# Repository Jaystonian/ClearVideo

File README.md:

# ClearVideo
Various S-Video devices

2020-10-04 
 * Updated the schematics and pcb to show I am using a 74F04, not a 74F06.. It has always been a '04.
 * Updated CV128 layout slightly.

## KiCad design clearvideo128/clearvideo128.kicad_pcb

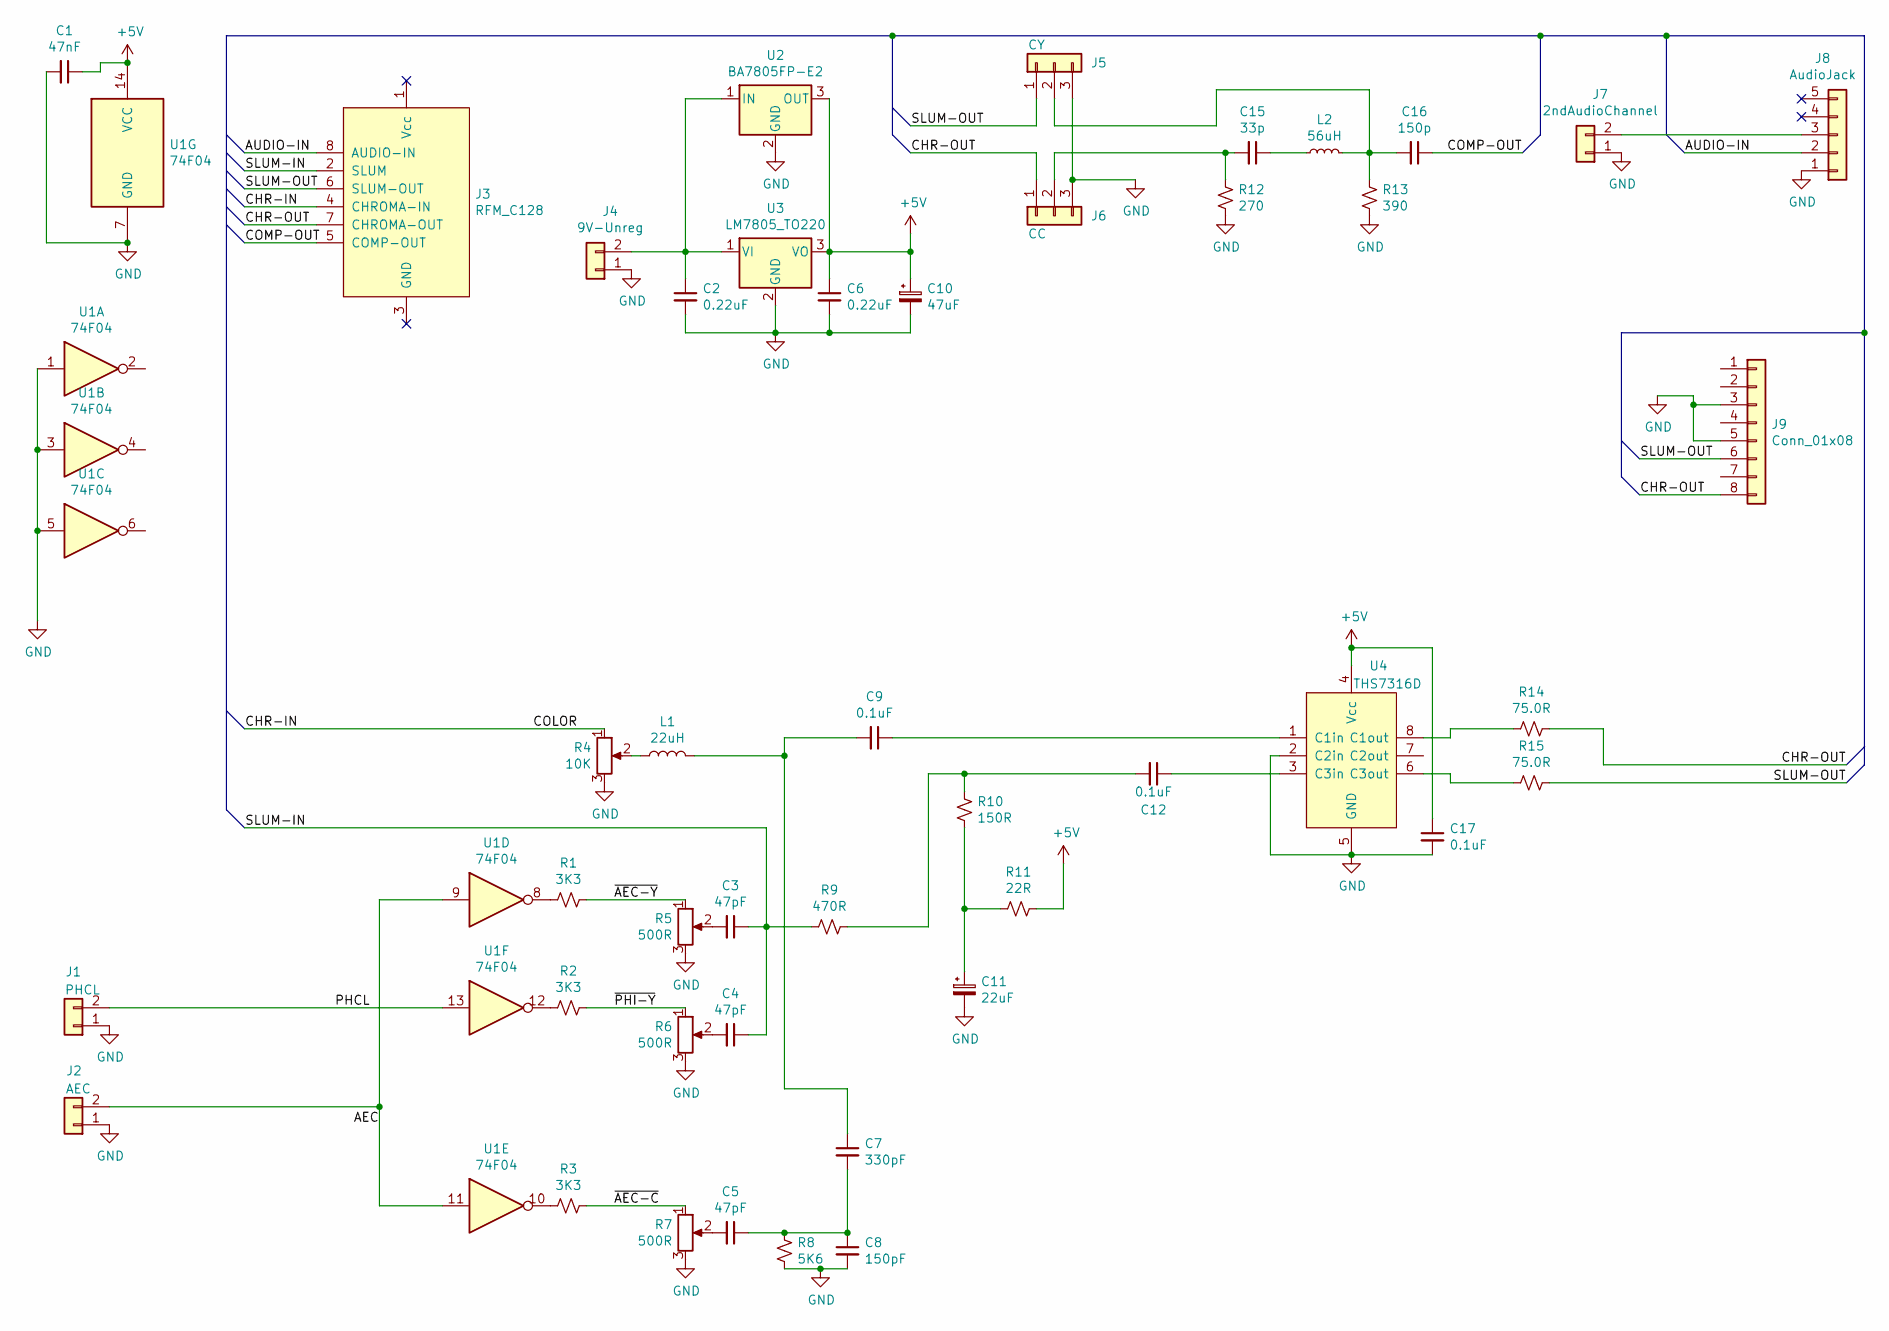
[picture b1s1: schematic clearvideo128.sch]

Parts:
C1: 47nF; C_0805_2012Metric_Pad1.15x1.40mm_HandSolder
C2, C6: 0.22uF; C_0805_2012Metric_Pad1.15x1.40mm_HandSolder
C3, C4, C5: 47pF; C_0805_2012Metric_Pad1.15x1.40mm_HandSolder
C7: 330pF; C_0805_2012Metric_Pad1.15x1.40mm_HandSolder
C8: 150pF; C_0805_2012Metric_Pad1.15x1.40mm_HandSolder
C9, C12, C17: 0.1uF; C_0805_2012Metric_Pad1.15x1.40mm_HandSolder
C10: 47uF; CP_Radial_D6.3mm_P2.50mm
C11: 22uF; CP_EIA-6032-28_Kemet-C_Pad2.25x2.35mm_HandSolder
C15: 33p; C_0805_2012Metric_Pad1.15x1.40mm_HandSolder
C16: 150p; C_0805_2012Metric_Pad1.15x1.40mm_HandSolder
J1: PHCL; PinHeader_1x02_P2.54mm_Vertical
J2: AEC; PinHeader_1x02_P2.54mm_Vertical
J3: RFM_C128
J4: 9V-Unreg; PinHeader_1x02_P2.54mm_Vertical
J5: CY; PinHeader_1x03_P2.54mm_Vertical
J6: CC; PinHeader_1x03_P2.54mm_Vertical
J7: 2ndAudioChannel; PinHeader_1x02_P2.54mm_Vertical
J8: AudioJack; Audio_SJ1-3535NG
J9: Conn_01x08; SVIDEO_PORT_KMDGX-4S-BS
L1: 22uH; L_Axial_L5.3mm_D2.2mm_P7.62mm_Horizontal_Vishay_IM-1
L2: 56uH; L_0805_2012Metric_Pad1.15x1.40mm_HandSolder
R1, R2, R3: 3K3; R_0805_2012Metric_Pad1.15x1.40mm_HandSolder
R4: 10K; Potentiometer_Bourns_3296X_Horizontal
R5, R6, R7: 500R; Potentiometer_Bourns_3296X_Horizontal
R8: 5K6; R_0805_2012Metric_Pad1.15x1.40mm_HandSolder
R9: 470R; R_0805_2012Metric_Pad1.15x1.40mm_HandSolder
R10: 150R; R_0805_2012Metric_Pad1.15x1.40mm_HandSolder
R11: 22R; R_0805_2012Metric_Pad1.15x1.40mm_HandSolder
R12: 270; R_0805_2012Metric_Pad1.15x1.40mm_HandSolder
R13: 390; R_0805_2012Metric_Pad1.15x1.40mm_HandSolder
R14, R15: 75.0R; R_Axial_DIN0207_L6.3mm_D2.5mm_P7.62mm_Horizontal
U1: 74F04; SOIC-14_3.9x8.7mm_P1.27mm
U2: BA7805FP-E2; TO-252-3_TabPin2
U3: LM7805_TO220; TO-220-3_Vertical
U4: THS7316D; SO-8_3.9x4.9mm_P1.27mm

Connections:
+5V: C1.1, C6.1, C10.1, C17.1, R11.1, U1.14 (VCC), U2.3 (OUT), U3.3 (VO), U4.4 (Vcc)
/AEC: J2.2, U1.9, U1.11; also elsewhere on the board
/AUDIO-IN: J3.8 (AUDIO-IN), J8.2
/CHR-IN: J3.4 (CHROMA-IN), R4.1
/CHR-OUT: J3.7 (CHROMA-OUT), J6.1, J9.8, R14.1
/COMP-OUT: C16.1, J3.5 (COMP-OUT)
/PHCL: J1.2, U1.13; also elsewhere on the board
/SLUM-IN: C3.1, C4.1, J3.2 (SLUM), R9.2
/SLUM-OUT: J3.6 (SLUM-OUT), J5.1, J9.6, R15.2
/~AEC-C: R3.1, R7.1
/~AEC-Y: R1.1, R5.1
/~PHI-Y: R2.1, R6.1
GND: C1.2, C2.2, C6.2, C8.2, C10.2, C11.2, C17.2, J1.1, J2.1, J4.1, J5.3, J6.3, J7.1, J8.1, J9.3, J9.5, R4.3, R5.3, R6.3, R7.3, R8.1, R12.2, R13.2, U1.1, U1.3, U1.5, U1.7 (GND), U2.2 (GND), U3.2 (GND), U4.2 (C2in), U4.5 (GND); also elsewhere on the board
unnamed 13: C2.1, J4.2, U2.1 (IN), U3.1 (VI); also elsewhere on the board
unnamed: C3.2, R5.2
unnamed: C4.2, R6.2
unnamed: C5.1, C7.2, C8.1, R8.2
unnamed: C5.2, R7.2
unnamed: C7.1, C9.2, L1.2
unnamed: C9.1, U4.1 (C1in)
unnamed: C11.1, R10.2, R11.2
unnamed: C12.1, U4.3 (C3in)
unnamed: C12.2, R9.1, R10.1
unnamed: C15.1, L2.1
unnamed: C15.2, J6.2, R12.1
unnamed: C16.2, J5.2, L2.2, R13.1
unnamed 28: J7.2, J8.3; also elsewhere on the board
unnamed: L1.1, R4.2
unnamed: R1.2, U1.8
unnamed: R2.2, U1.12
unnamed: R3.2, U1.10
unnamed: R14.2, U4.8 (C1out)
unnamed: R15.1, U4.6 (C3out)

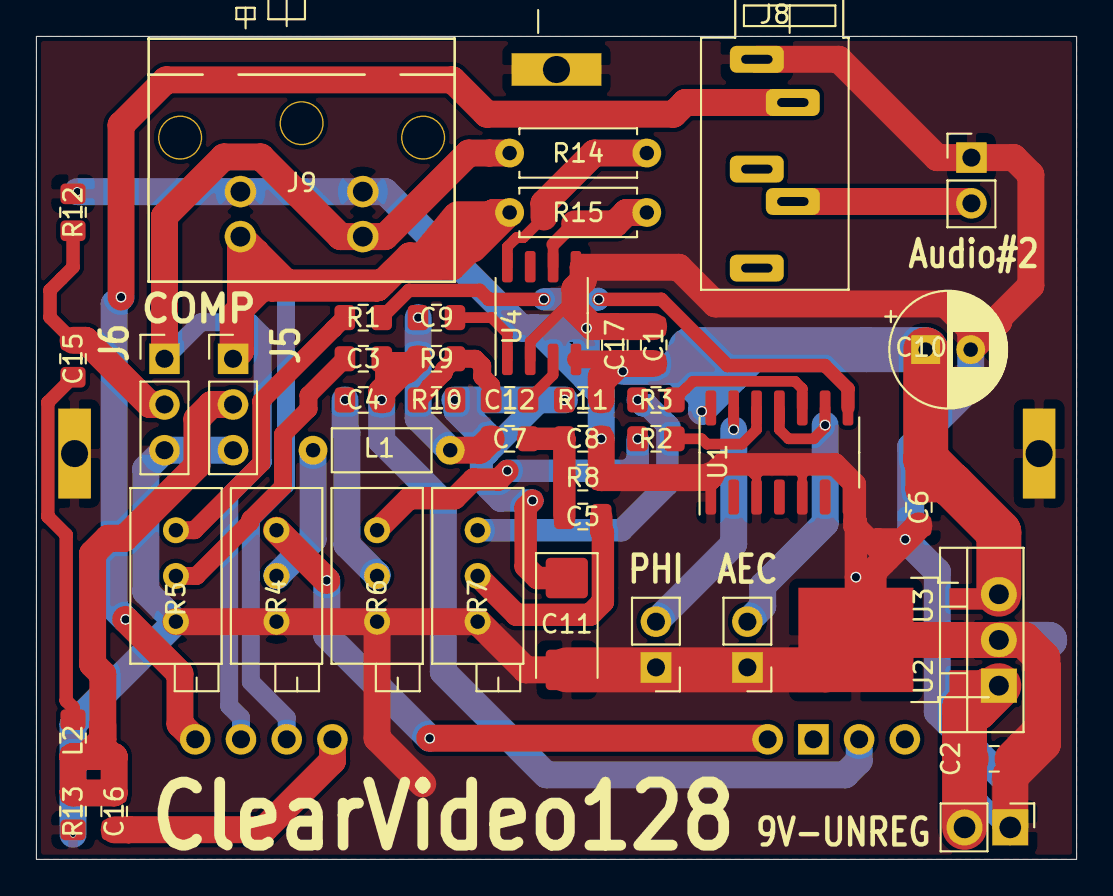
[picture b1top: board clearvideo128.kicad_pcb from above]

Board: 2 copper layers, 57.8 x 45.7 mm, 45 parts (0 on the bottom side), 33 nets.

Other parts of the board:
9V-UNREG: 9V-Unreg; PinHeader_1x02_P2.54mm_Vertical
AEC: AEC; PinHeader_1x02_P2.54mm_Vertical
Audio#2: 2ndAudioChannel; PinHeader_1x02_P2.54mm_Vertical
PHI: PHCL; PinHeader_1x02_P2.54mm_Vertical

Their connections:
/AEC: AEC.2; also elsewhere on the board
/PHCL: PHI.2; also elsewhere on the board
GND: 9V-UNREG.1, AEC.1, Audio#2.1, PHI.1; also elsewhere on the board
unnamed 13: 9V-UNREG.2; also elsewhere on the board
unnamed 28: Audio#2.2; also elsewhere on the board

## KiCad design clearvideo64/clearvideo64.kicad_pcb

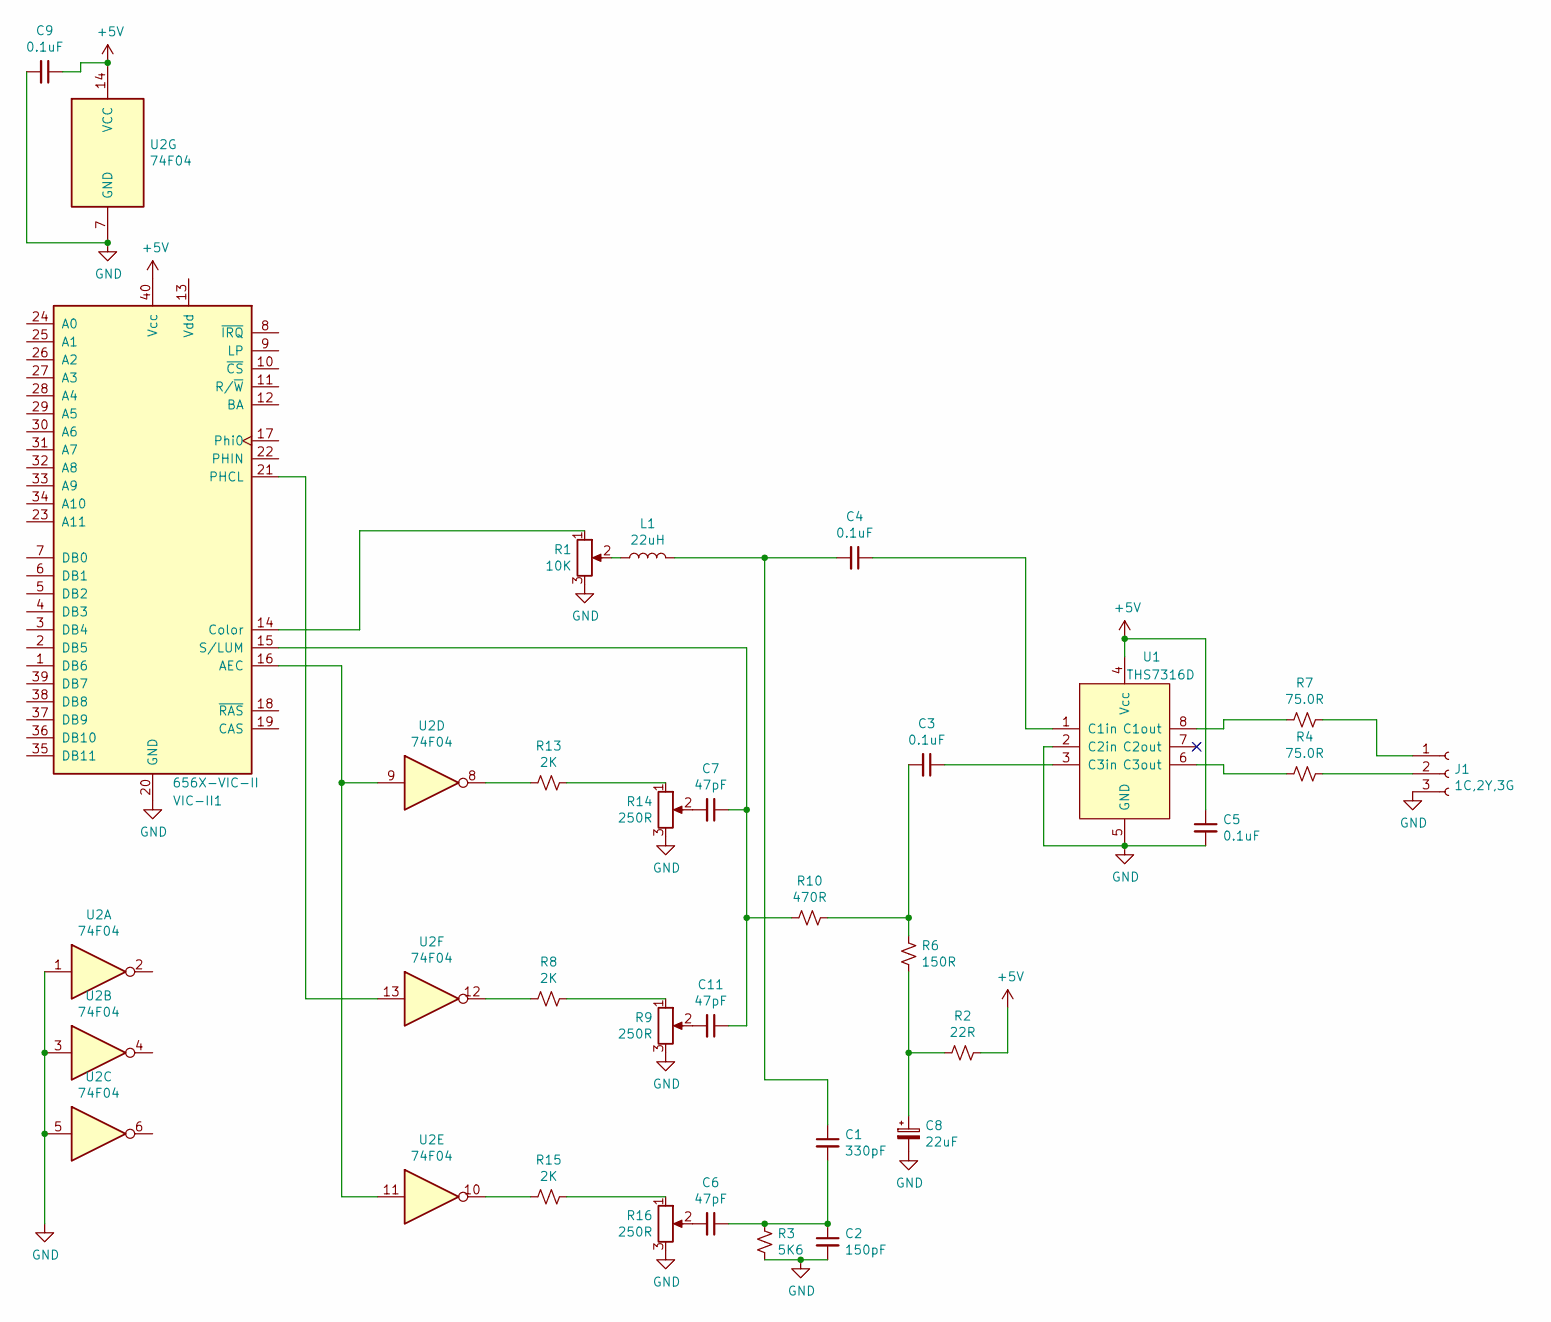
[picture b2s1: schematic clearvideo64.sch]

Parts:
C1: 330pF; C_0805_2012Metric_Pad1.15x1.40mm_HandSolder
C2: 150pF; C_0805_2012Metric_Pad1.15x1.40mm_HandSolder
C3, C4, C5, C9: 0.1uF; C_0805_2012Metric_Pad1.15x1.40mm_HandSolder
C6, C7, C11: 47pF; C_0805_2012Metric_Pad1.15x1.40mm_HandSolder
C8: 22uF; CP_EIA-6032-28_Kemet-C_Pad2.25x2.35mm_HandSolder
J1: 1C,2Y,3G; VideoOutHeader_1x03
L1: 22uH; L_Axial_L5.3mm_D2.2mm_P7.62mm_Horizontal_Vishay_IM-1
R1: 10K; Potentiometer_Bourns_3296X_Horizontal
R2: 22R; R_0805_2012Metric_Pad1.15x1.40mm_HandSolder
R3: 5K6; R_0805_2012Metric_Pad1.15x1.40mm_HandSolder
R4, R7: 75.0R; R_Axial_DIN0207_L6.3mm_D2.5mm_P7.62mm_Horizontal
R6: 150R; R_0805_2012Metric_Pad1.15x1.40mm_HandSolder
R8, R13, R15: 2K; R_0805_2012Metric_Pad1.15x1.40mm_HandSolder
R9, R14, R16: 250R; Potentiometer_Bourns_3296X_Horizontal
R10: 470R; R_0805_2012Metric_Pad1.15x1.40mm_HandSolder
U1: THS7316D; SO-8_3.9x4.9mm_P1.27mm
U2: 74F04; SOIC-14_3.9x8.7mm_P1.27mm
VIC-II1: 656X-VIC-II; DIP-40_W15.24mm

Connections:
+5V: C5.1, C9.1, R2.1, U1.4 (Vcc), U2.14 (VCC), VIC-II1.40 (Vcc)
GND: C2.2, C5.2, C8.2, C9.2, J1.3, R1.3, R3.1, R9.3, R14.3, R16.3, U1.2 (C2in), U1.5 (GND), U2.1, U2.3, U2.5, U2.7 (GND), VIC-II1.20 (GND)
unnamed: C1.1, C4.2, L1.2
unnamed: C1.2, C2.1, C6.1, R3.2
unnamed: C3.1, U1.3 (C3in)
unnamed: C3.2, R6.1, R10.1
unnamed: C4.1, U1.1 (C1in)
unnamed: C6.2, R16.2
unnamed: C7.2, R14.2
unnamed: C8.1, R2.2, R6.2
unnamed: C7.1, C11.1, R10.2, VIC-II1.15 (S/LUM)
unnamed: C11.2, R9.2
unnamed: J1.1, R7.1
unnamed: J1.2, R4.2
unnamed: L1.1, R1.2
unnamed: R1.1, VIC-II1.14 (Color)
unnamed: R4.1, U1.6 (C3out)
unnamed: R7.2, U1.8 (C1out)
unnamed: R8.1, R9.1
unnamed: R8.2, U2.12
unnamed: R13.1, R14.1
unnamed: R13.2, U2.8
unnamed: R15.1, R16.1
unnamed: R15.2, U2.10
unnamed: U2.9, U2.11, VIC-II1.16 (AEC)
unnamed: U2.13, VIC-II1.21 (PHCL)

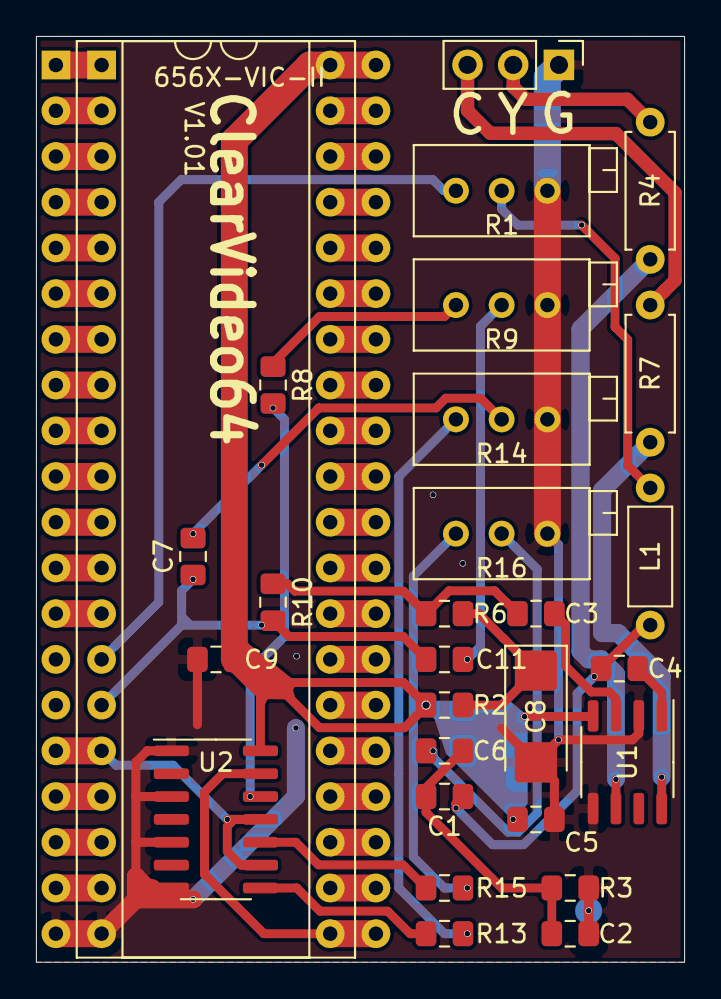
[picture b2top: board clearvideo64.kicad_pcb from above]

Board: 2 copper layers, 36.0 x 51.4 mm, 28 parts (0 on the bottom side), 26 nets.

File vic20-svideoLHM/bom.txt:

Most SMD are 2012 metric
22uF SMD is 6032 Kemet 

75.0R	0.302	2	r4,r7
THS7316D	0.852	1	u1
74LVC06	0.255	1	u2

R2	22R
R6	150R
R13	2K
R15	2K
R8	2K
R14	250R
R9	250R
R10	470R
R3	5K6

R16	250R
R1	10K

L1	22uH

C1	330pF
C2	150pF
C3	0.1uF
C4	0.1uF
C5	0.1uF
C6	47pF
C7	47pF
C8	22uF
C9	0.1uF
C11	47pF

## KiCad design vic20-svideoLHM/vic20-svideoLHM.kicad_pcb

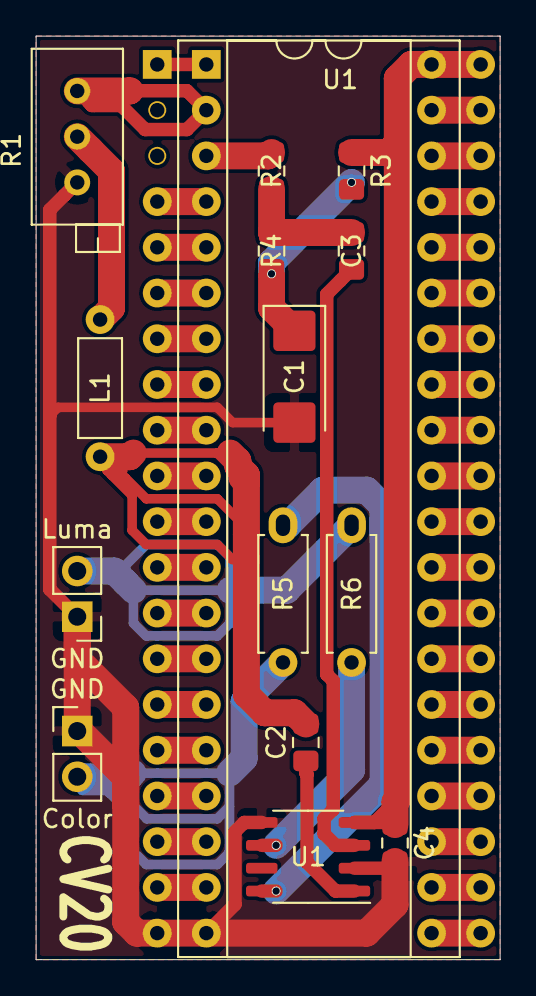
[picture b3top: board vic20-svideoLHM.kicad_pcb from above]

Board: 2 copper layers, 25.8 x 51.3 mm, 16 parts (0 on the bottom side), 50 nets.

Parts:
C1: 22uF; CP_EIA-6032-28_Kemet-C_Pad2.25x2.35mm_HandSolder
C2, C3, C4: 0.1uF; C_0805_2012Metric_Pad1.15x1.40mm_HandSolder
GND: Color; PinHeader_1x02_P2.54mm_Vertical
GND#2: Luma; PinHeader_1x02_P2.54mm_Vertical
L1: 22uH; L_Axial_L5.3mm_D2.2mm_P7.62mm_Horizontal_Vishay_IM-1
R1: 10K; Potentiometer_Bourns_3296X_Horizontal
R2: 470R; R_0805_2012Metric_Pad1.15x1.40mm_HandSolder
R3: 22R; R_0805_2012Metric_Pad1.15x1.40mm_HandSolder
R4: 150R; R_0805_2012Metric_Pad1.15x1.40mm_HandSolder
R5, R6: 75.0R; R_Axial_DIN0207_L6.3mm_D2.5mm_P7.62mm_Horizontal
U1: THS7316D; SO-8_3.9x4.9mm_P1.27mm
U1#2: 656X-VIC-I; DIP-40_W15.24mm
U-SOCKET1: 656X-VIC-I; DIP-40_W15.24mm

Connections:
+5V: C4.1, R3.1, U1.4, U1#2.40, U-SOCKET1.40
/A0: U1#2.21, U-SOCKET1.21
/A1: U1#2.22, U-SOCKET1.22
/A2: U1#2.23, U-SOCKET1.23
/A3: U1#2.24, U-SOCKET1.24
/A4: U1#2.25, U-SOCKET1.25
/A5: U1#2.26, U-SOCKET1.26
/A6: U1#2.27, U-SOCKET1.27
/A7: U1#2.28, U-SOCKET1.28
/A8: U1#2.29, U-SOCKET1.29
/A9: U1#2.30, U-SOCKET1.30
/A10: U1#2.31, U-SOCKET1.31
/A11: U1#2.32, U-SOCKET1.32
/A12: U1#2.33, U-SOCKET1.33
/A13: U1#2.34, U-SOCKET1.34
/Audio: U1#2.19, U-SOCKET1.19
/Color: R1.1, U1#2.2
/D0: U1#2.16, U-SOCKET1.16
/D1: U1#2.15, U-SOCKET1.15
/D2: U1#2.14, U-SOCKET1.14
/D3: U1#2.13, U-SOCKET1.13
/D4: U1#2.12, U-SOCKET1.12
/D5: U1#2.11, U-SOCKET1.11
/D6: U1#2.10, U-SOCKET1.10
/D7: U1#2.9, U-SOCKET1.9
/D8: U1#2.8, U-SOCKET1.8
/D9: U1#2.7, U-SOCKET1.7
/D10: U1#2.6, U-SOCKET1.6
/D11: U1#2.5, U-SOCKET1.5
/Luma: R2.2, U1#2.3
/NC: U1#2.1, U-SOCKET1.1
/Option: U1#2.37, U-SOCKET1.37
/PPhi1: U1#2.35, U-SOCKET1.35
/PPhi2: U1#2.36, U-SOCKET1.36
/Phi1: U1#2.39, U-SOCKET1.39
/Phi2: U1#2.38, U-SOCKET1.38
/PotX: U1#2.17, U-SOCKET1.17
/PotY: U1#2.18, U-SOCKET1.18
/R~W~: U1#2.4, U-SOCKET1.4
GND: C1.2, C4.2, GND.1, GND#2.1, R1.3, U1.2, U1.5, U1#2.20, U-SOCKET1.20
unnamed: C1.1, R3.2, R4.2
unnamed: C2.1, U1.1
unnamed: C2.2, L1.2
unnamed: C3.1, U1.3
unnamed: C3.2, R2.1, R4.1
unnamed: GND.2, R5.1
unnamed: GND#2.2, R6.2
unnamed: L1.1, R1.2
unnamed: R5.2, U1.8
unnamed: R6.1, U1.6

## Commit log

2023-06-06 Update clearvideo64
    Corrected "74LVC06" to "74LVC04"
2023-06-06 Update clearvideo64.xml
    Corrected U2 value "74LVC06" to "74LVC04"
